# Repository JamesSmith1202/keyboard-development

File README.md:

# keyboard-development
Personal repo for keyboard development projects

## Soup-Board

### Goal Criteria
- Key capacity of a 65%
- Arrow keys without layer
- Trackpad
- Split
- Rotary encoder switch for volume
- OLED screen for stupid shit
- Modular thumb cluster
- USB C for ports

### Resources
- [swillkb case and faceplate generator](http://builder.swillkb.com/)
- [Bill of Materials](https://docs.google.com/spreadsheets/d/1uKeJ7xrDS6hyHrwxc7NrY-vNozwYZxpyhtZBO_KHwDQ/edit#gid=0)
- [Moonlander Keyboard Layout](http://www.keyboard-layout-editor.com/##@_backcolor=%23ffffff&name=Moonlander&switchMount=cherry%3B&@_x:3&a:7&f:4%3B&=&_x:8.25%3B&=%3B&@_y:-0.875&x:2%3B&=&_x:1%3B&=&_x:6.25%3B&=&_x:1%3B&=%3B&@_y:-0.875&x:5%3B&=&_x:4.25%3B&=%3B&@_y:-0.875&f:5%3B&=&_f:4%3B&=&_x:12.25%3B&=&_f:6%3B&=%3B&@_y:-0.875&x:6&f:3%3B&=&_x:2.25%3B&=%3B&@_y:-0.5&x:3&t=%230000ff&f:7%3B&=&_x:8.25%3B&=%3B&@_y:-0.875&x:2%3B&=&_x:1%3B&=&_x:6.25%3B&=&_x:1%3B&=%3B&@_y:-0.875&x:5%3B&=&_x:4.25%3B&=%3B&@_y:-0.875&t=%23000000&f:6%3B&=&_t=%230000ff&f:7%3B&=&_x:12.25%3B&=&_t=%23000000&f:6%3B&=%3B&@_y:-0.875&x:6&t=%230000ff&f:4%3B&=&_x:2.25&t=%23000000%3B&=%3B&@_y:-0.5&x:3&t=%230000ff&f:6%3B&=&_x:8.25&f:7%3B&=%3B&@_y:-0.875&x:2&f:6%3B&=&_x:1&f:7%3B&=&_x:6.25%3B&=&_x:1%3B&=%3B&@_y:-0.875&x:5&f:6%3B&=&_x:4.25&f:7%3B&=%3B&@_y:-0.875&t=%23000000&f:6%3B&=&_t=%230000ff&f:7%3B&=&_x:12.25&f:6%3B&=&_t=%23000000%3B&=%3B&@_y:-0.875&x:6&t=%230000ff&f:4%3B&=&_x:2.25&t=%23000000%3B&=%3B&@_y:-0.5&x:3&t=%230000ff&f:7%3B&=&_x:8.25&f:6%3B&=%3B&@_y:-0.875&x:2&f:7%3B&=&_x:1&f:6%3B&=&_x:6.25&f:7%3B&=&_x:1&f:6%3B&=%3B&@_y:-0.875&x:5%3B&=&_x:4.25&f:7%3B&=%3B&@_y:-0.875&t=%23000000&f:6%3B&=&_t=%230000ff&f:7%3B&=&_x:12.25&f:6%3B&=&_t=%23000000&f:9%3B&=%3B&@_y:-0.375&x:3&f:6%3B&=&_x:8.25&f:9%3B&=%3B&@_y:-0.875&x:2&f:6%3B&=&_x:1%3B&=&_x:6.25%3B&=&_x:1&f:9%3B&=%3B&@_y:-0.75&f:2%3B&=&_f:6%3B&=&_x:12.25&f:9%3B&=&=%3B&@_r:45&rx:6&ry:4.25&y:-0.5&f:4&w:2%3B&=%3B&@_f:6&h:1.5%3B&=&_h:1.5%3B&=&_f:9&h:1.5%3B&=%3B&@_r:-45&rx:10.25&y:-0.5&x:-2&f:6&w:2%3B&=%3B&@_x:-3&h:1.5%3B&=&_f:4&h:1.5%3B&=&_f:6&h:1.5%3B&=)

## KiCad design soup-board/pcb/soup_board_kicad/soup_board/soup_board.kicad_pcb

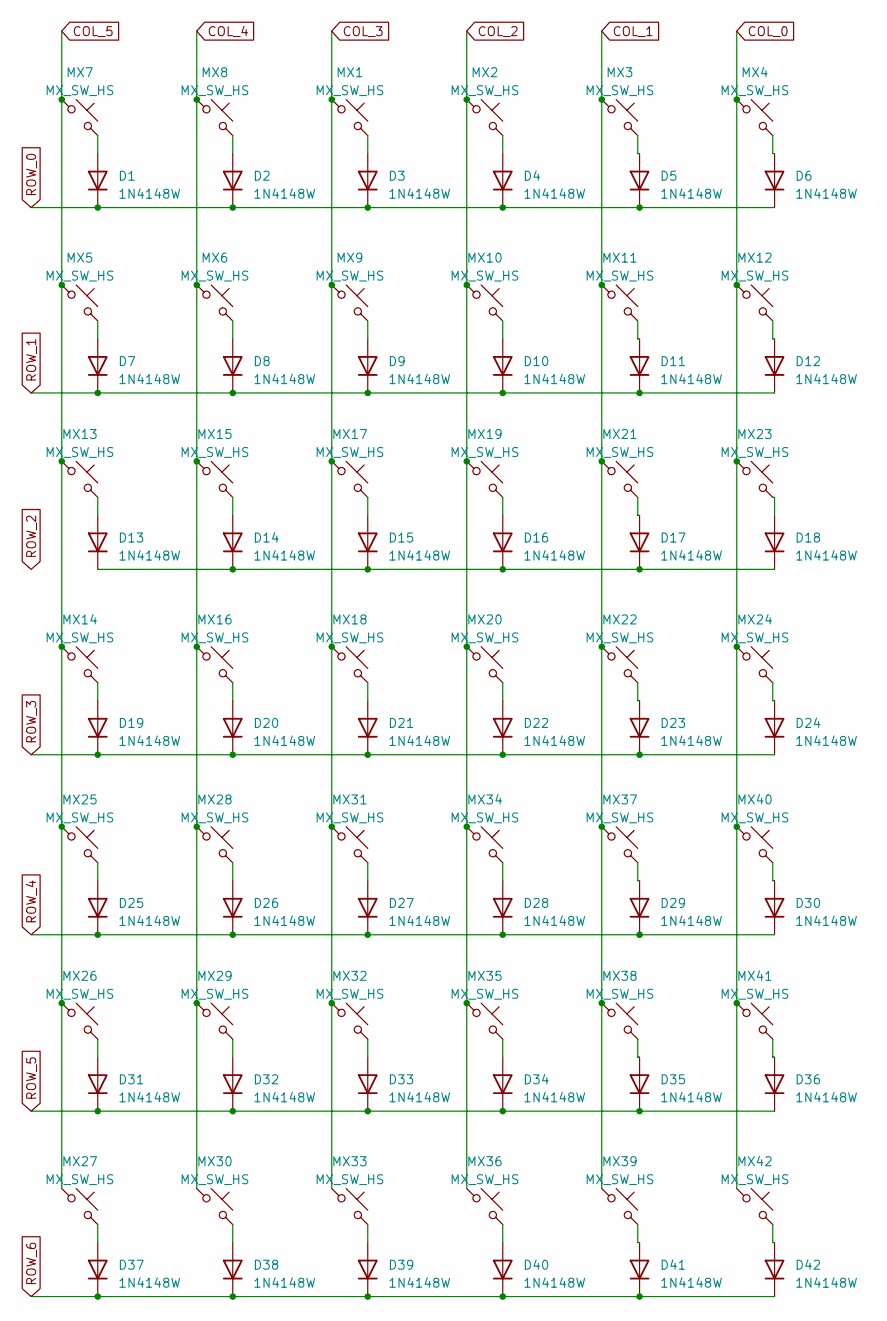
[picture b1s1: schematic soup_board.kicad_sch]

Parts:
D1, D2, D3, D4, D5, D6, D7, D8, D9, D10, D11, D12, D13, D14, D15, D16, D17, D18, D19, D20, D21, D22, D23, D24, D25, D26, D27, D28, D29, D30, D31, D32, D33, D34, D35, D36, D37, D38, D39, D40, D41, D42: 1N4148W; D_SOD-123
MX1, MX2, MX3, MX4, MX5, MX6, MX7, MX8, MX9, MX10, MX11, MX12, MX13, MX14, MX15, MX16, MX17, MX18, MX19, MX20, MX21, MX22, MX23, MX24, MX25, MX26, MX27, MX28, MX29, MX30, MX31, MX32, MX33, MX34, MX35, MX36, MX37, MX38, MX39, MX40, MX41, MX42: MX_SW_HS; SW_MX_HS_1u

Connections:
COL_0: MX4.1, MX12.1, MX23.1, MX24.1, MX40.1, MX41.1, MX42.1
COL_1: MX3.1, MX11.1, MX21.1, MX22.1, MX37.1, MX38.1, MX39.1
COL_2: MX2.1, MX10.1, MX19.1, MX20.1, MX34.1, MX35.1, MX36.1
COL_3: MX1.1, MX9.1, MX17.1, MX18.1, MX31.1, MX32.1, MX33.1
COL_4: MX6.1, MX8.1, MX15.1, MX16.1, MX28.1, MX29.1, MX30.1
COL_5: MX5.1, MX7.1, MX13.1, MX14.1, MX25.1, MX26.1, MX27.1
unnamed: D1.2 (A), MX7.2
unnamed: D2.2 (A), MX8.2
unnamed: D3.2 (A), MX1.2
unnamed: D4.2 (A), MX2.2
unnamed: D5.2 (A), MX3.2
unnamed: D6.2 (A), MX4.2
unnamed: D7.2 (A), MX5.2
unnamed: D8.2 (A), MX6.2
unnamed: D9.2 (A), MX9.2
unnamed: D10.2 (A), MX10.2
unnamed: D11.2 (A), MX11.2
unnamed: D12.2 (A), MX12.2
unnamed: D13.2 (A), MX13.2
unnamed: D13.1 (K), D14.1 (K), D15.1 (K), D16.1 (K), D17.1 (K), D18.1 (K)
unnamed: D14.2 (A), MX15.2
unnamed: D15.2 (A), MX17.2
unnamed: D16.2 (A), MX19.2
unnamed: D17.2 (A), MX21.2
unnamed: D18.2 (A), MX23.2
unnamed: D19.2 (A), MX14.2
unnamed: D20.2 (A), MX16.2
unnamed: D21.2 (A), MX18.2
unnamed: D22.2 (A), MX20.2
unnamed: D23.2 (A), MX22.2
unnamed: D24.2 (A), MX24.2
unnamed: D25.2 (A), MX25.2
unnamed: D26.2 (A), MX28.2
unnamed: D27.2 (A), MX31.2
unnamed: D28.2 (A), MX34.2
unnamed: D29.2 (A), MX37.2
unnamed: D30.2 (A), MX40.2
unnamed: D31.2 (A), MX26.2
unnamed: D32.2 (A), MX29.2
unnamed: D33.2 (A), MX32.2
unnamed: D34.2 (A), MX35.2
unnamed: D35.2 (A), MX38.2
unnamed: D36.2 (A), MX41.2
unnamed: D37.2 (A), MX27.2
unnamed: D38.2 (A), MX30.2
unnamed: D39.2 (A), MX33.2
unnamed: D40.2 (A), MX36.2
unnamed: D41.2 (A), MX39.2
unnamed: D42.2 (A), MX42.2
ROW_0: D1.1 (K), D2.1 (K), D3.1 (K), D4.1 (K), D5.1 (K), D6.1 (K)
ROW_1: D7.1 (K), D8.1 (K), D9.1 (K), D10.1 (K), D11.1 (K), D12.1 (K)
ROW_3: D19.1 (K), D20.1 (K), D21.1 (K), D22.1 (K), D23.1 (K), D24.1 (K)
ROW_4: D25.1 (K), D26.1 (K), D27.1 (K), D28.1 (K), D29.1 (K), D30.1 (K)
ROW_5: D31.1 (K), D32.1 (K), D33.1 (K), D34.1 (K), D35.1 (K), D36.1 (K)
ROW_6: D37.1 (K), D38.1 (K), D39.1 (K), D40.1 (K), D41.1 (K), D42.1 (K)

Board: 2 copper layers, 84 parts (0 on the bottom side), 55 nets, no tracks yet.

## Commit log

2023-05-04 intial commit with key layout and faceplate
2023-05-09 update and finish eagle schematic
2023-05-09 migrate design to kicad
2023-05-09 finished schematic for v0
